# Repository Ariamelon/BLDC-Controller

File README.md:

# BLDC motor controller
A brushless DC motor controller developed in partial fulfilment of the requirements for a degree of BEng (Hons) Electronic & Computer Engineering.

## Disclaimer
The hardware is licensed under CERN-OHL-S-2.0, and the firmware is licensed under GNU GPLv3. 

https://github.com/user-attachments/assets/5595b5e6-1121-481e-8a8e-658866d14e04

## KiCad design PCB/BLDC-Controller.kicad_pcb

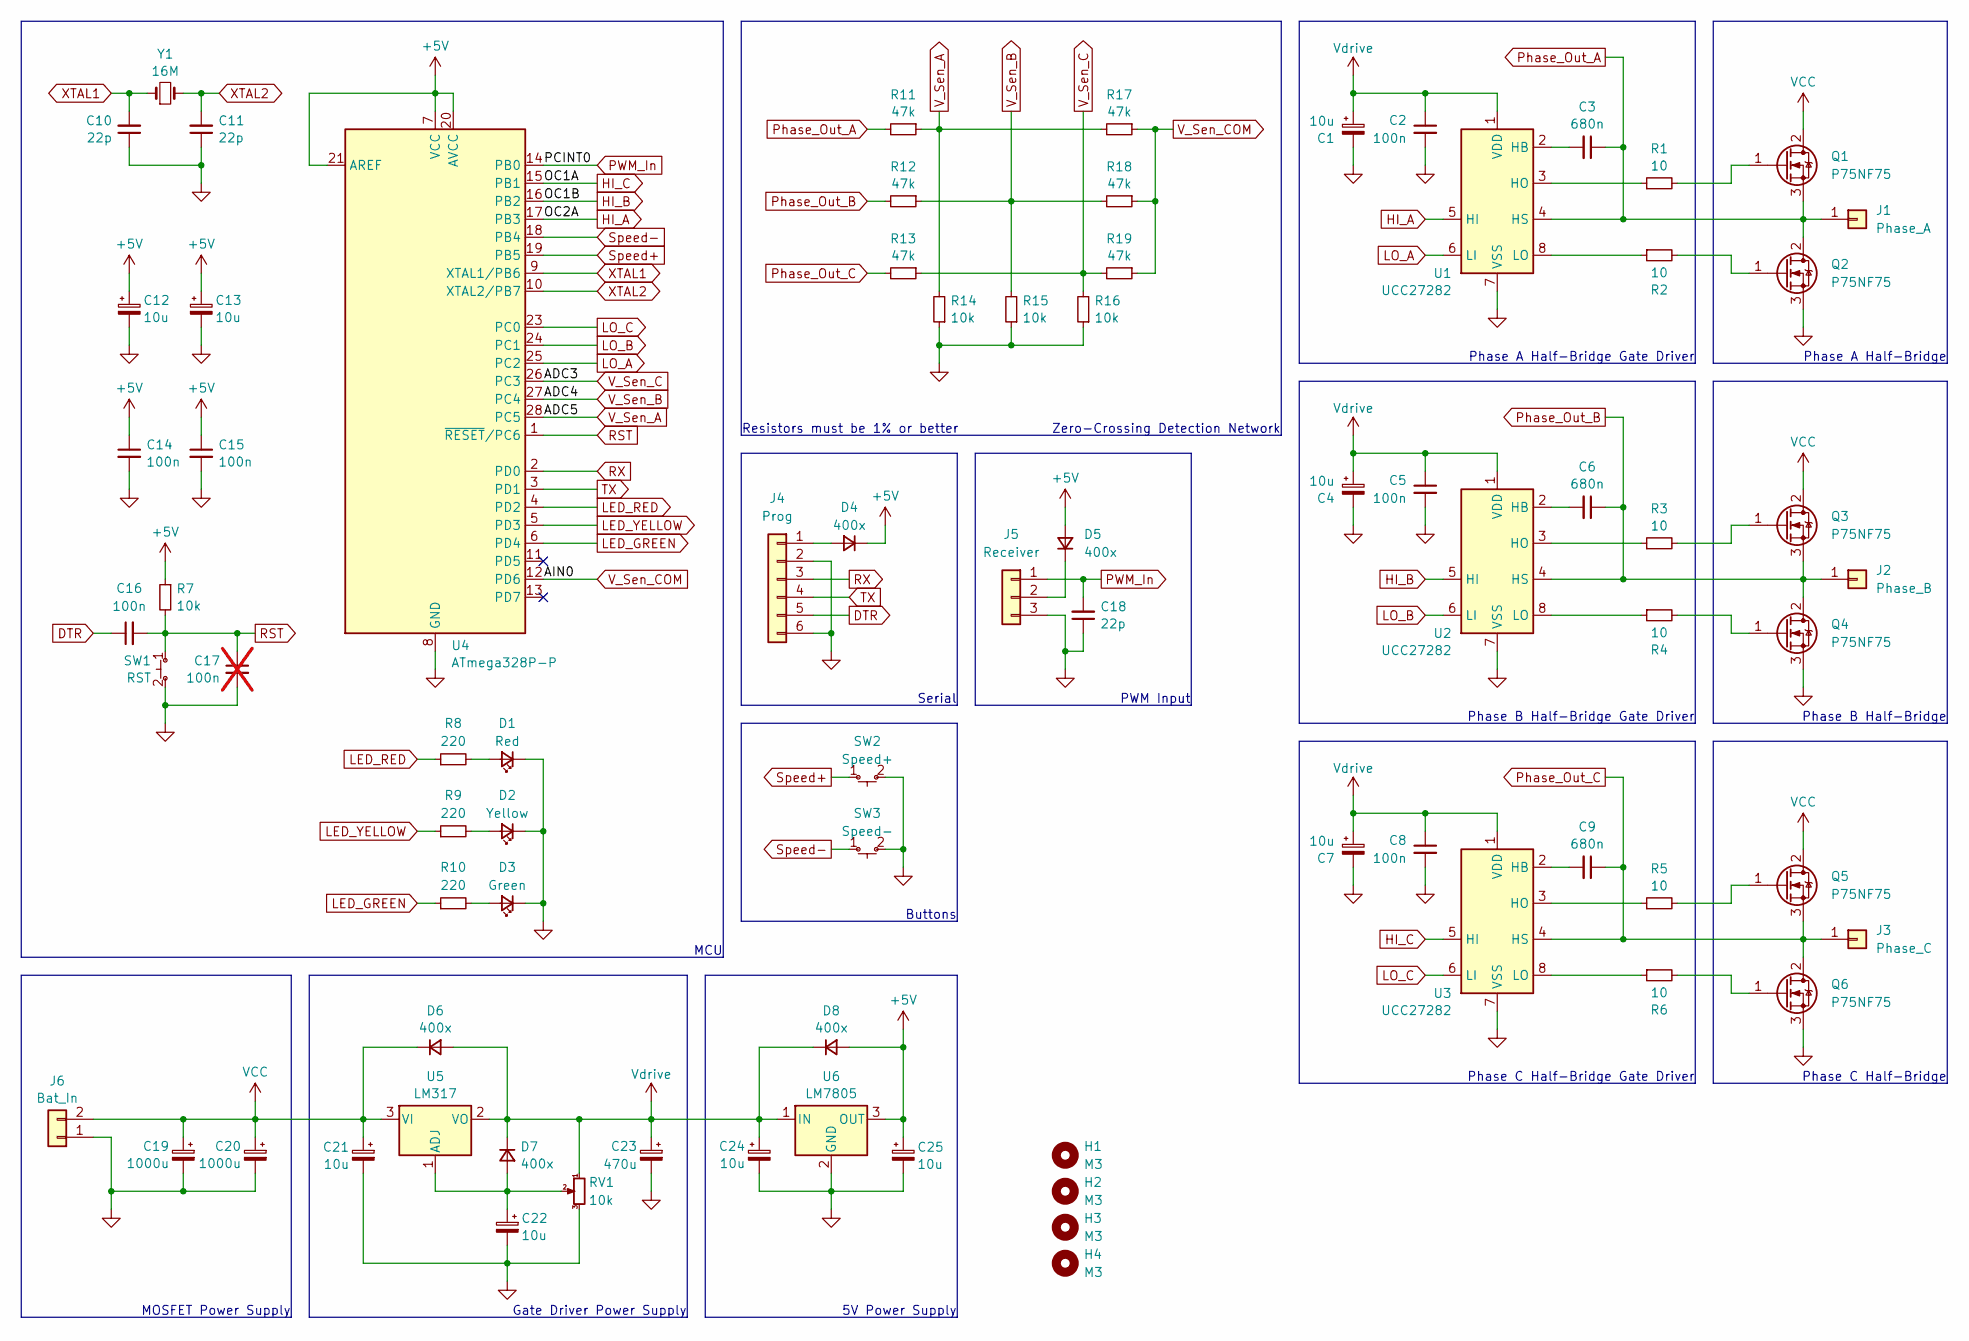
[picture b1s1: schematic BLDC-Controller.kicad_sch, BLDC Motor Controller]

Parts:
C1, C4, C7, C12, C13, C21, C22, C24, C25: 10u; CP_Radial_D5.0mm_P2.54mm
C2, C5, C8, C14, C15, C16: 100n; C_Disc_D6.0mm_W2.5mm_P5.08mm
C3, C6, C9: 680n; C_Rect_L7.0mm_W4.5mm_P5.08mm
C10, C11, C18: 22p; C_Disc_D5.0mm_W2.5mm_P2.54mm
C17: 100n; C_Disc_D6.0mm_W2.5mm_P5.08mm; not fitted
C19, C20: 1000u; CP_Radial_D16.0mm_P7.62mm
C23: 470u; CP_Radial_D10.0mm_P5.00mm
D1: Red; LED_D3.0mm
D2: Yellow; LED_D3.0mm
D3: Green; LED_D3.0mm
D4, D5, D6, D7, D8: 400x; D_DO-35_SOD27_P7.62mm_Horizontal
H1, H2, H3, H4: M3; MountingHole_3.2mm_M3_Pad
J1: Phase_A; TestPoint_Pad_4.0x4.0mm
J2: Phase_B; TestPoint_Pad_4.0x4.0mm
J3: Phase_C; TestPoint_Pad_4.0x4.0mm
J4: Prog; PinHeader_1x06_P2.54mm_Vertical
J5: Receiver; PinHeader_1x03_P2.54mm_Vertical
J6: Bat_In; AMASS_XT60-M_1x02_P7.20mm_Vertical
Q1, Q2, Q3, Q4, Q5, Q6: P75NF75; TO-220-3_Vertical
R1, R2, R3, R4, R5, R6: 10; R_Axial_DIN0204_L3.6mm_D1.6mm_P7.62mm_Horizontal
R7, R14, R15, R16: 10k; R_Axial_DIN0204_L3.6mm_D1.6mm_P7.62mm_Horizontal
R8, R9, R10: 220; R_Axial_DIN0204_L3.6mm_D1.6mm_P7.62mm_Horizontal
R11, R12, R13, R17, R18, R19: 47k; R_Axial_DIN0204_L3.6mm_D1.6mm_P7.62mm_Horizontal
RV1: 10k; Potentiometer_Piher_PT-10-V10_Vertical
SW1: RST; SW_PUSH_6mm
SW2: Speed+; SW_PUSH_6mm
SW3: Speed-; SW_PUSH_6mm
U1, U2, U3: UCC27282; DIP-8_W7.62mm_Socket
U4: ATmega328P-P; DIP-28_W7.62mm_Socket
U5: LM317; TO-220-3_Vertical
U6: LM7805; TO-220-3_Vertical
Y1: 16M; Crystal_HC49-4H_Vertical

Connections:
+5V: C12.1, C13.1, C14.1, C15.1, C25.1, D4.1 (K), D5.2 (A), D8.2 (A), R7.1, U4.7 (VCC), U4.20 (AVCC), U4.21 (AREF), U6.3 (OUT)
DTR: C16.1, J4.5
GND: C1.2, C2.2, C4.2, C5.2, C7.2, C8.2, C10.1, C11.1, C12.2, C13.2, C14.2, C15.2, C17.2, C18.1, C19.2, C20.2, C21.2, C22.2, C23.2, C24.2, C25.2, D1.1 (K), D2.1 (K), D3.1 (K), J4.2, J4.6, J5.3, J6.1, Q2.3 (S), Q4.3 (S), Q6.3 (S), R14.1, R15.1, R16.1, RV1.3, SW1.2 (B), SW2.2 (B), SW3.2 (B), U1.7 (VSS), U1.9 (EP), U2.7 (VSS), U2.9 (EP), U3.7 (VSS), U3.9 (EP), U4.8 (GND), U4.22 (GND), U6.2 (GND)
HI_A: U1.5 (HI), U4.17 (PB3)
HI_B: U2.5 (HI), U4.16 (PB2)
HI_C: U3.5 (HI), U4.15 (PB1)
LED_GREEN: R10.1, U4.6 (PD4)
LED_RED: R8.1, U4.4 (PD2)
LED_YELLOW: R9.1, U4.5 (PD3)
LO_A: U1.6 (LI), U4.25 (PC2)
LO_B: U2.6 (LI), U4.24 (PC1)
LO_C: U3.6 (LI), U4.23 (PC0)
unnamed: D1.2 (A), R8.2
unnamed: D2.2 (A), R9.2
unnamed: D3.2 (A), R10.2
unnamed: D4.2 (A), J4.1
unnamed: D5.1 (K), J5.2
unnamed: C22.1, D7.2 (A), RV1.2, U5.1 (ADJ)
unnamed: Q1.1 (G), R1.2
unnamed: Q2.1 (G), R2.2
unnamed: Q3.1 (G), R3.2
unnamed: Q4.1 (G), R4.2
unnamed: Q5.1 (G), R5.2
unnamed: Q6.1 (G), R6.2
unnamed: C3.2, U1.2 (HB)
unnamed: R1.1, U1.3 (HO)
unnamed: R2.1, U1.8 (LO)
unnamed: C6.2, U2.2 (HB)
unnamed: R3.1, U2.3 (HO)
unnamed: R4.1, U2.8 (LO)
unnamed: C9.2, U3.2 (HB)
unnamed: R5.1, U3.3 (HO)
unnamed: R6.1, U3.8 (LO)
PWM_In: C18.2, J5.1, U4.14 (PB0)
Phase_Out_A: C3.1, J1.1, Q1.3 (S), Q2.2 (D), R11.2, U1.4 (HS)
Phase_Out_B: C6.1, J2.1, Q3.3 (S), Q4.2 (D), R12.2, U2.4 (HS)
Phase_Out_C: C9.1, J3.1, Q5.3 (S), Q6.2 (D), R13.2, U3.4 (HS)
RST: C16.2, C17.1, R7.2, SW1.1 (A), U4.1 (~RESET/PC6)
RX: J4.3, U4.2 (PD0)
Speed+: SW2.1 (A), U4.19 (PB5)
Speed-: SW3.1 (A), U4.18 (PB4)
TX: J4.4, U4.3 (PD1)
VCC: C19.1, C20.1, C21.1, D6.1 (K), J6.2, Q1.2 (D), Q3.2 (D), Q5.2 (D), U5.3 (VI)
V_Sen_A: R11.1, R14.2, R17.2, U4.28 (PC5)
V_Sen_B: R12.1, R15.2, R18.2, U4.27 (PC4)
V_Sen_C: R13.1, R16.2, R19.2, U4.26 (PC3)
V_Sen_COM: R17.1, R18.1, R19.1, U4.12 (PD6)
Vdrive: C1.1, C2.1, C4.1, C5.1, C7.1, C8.1, C23.1, C24.1, D6.2 (A), D7.1 (K), D8.1 (K), RV1.1, U1.1 (VDD), U2.1 (VDD), U3.1 (VDD), U5.2 (VO), U6.1 (IN)
XTAL1: C10.2, U4.9 (XTAL1/PB6), Y1.1
XTAL2: C11.2, U4.10 (XTAL2/PB7), Y1.2

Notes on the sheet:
MOSFET Power Supply
Gate Driver Power Supply
Resistors must be 1% or better
5V Power Supply
PWM Input
Buttons
Phase A Half-Bridge Gate Driver
Serial
Zero-Crossing Detection Network
Phase C Half-Bridge Gate Driver
Phase C Half-Bridge
Phase A Half-Bridge
Phase B Half-Bridge
Phase B Half-Bridge Gate Driver
MCU

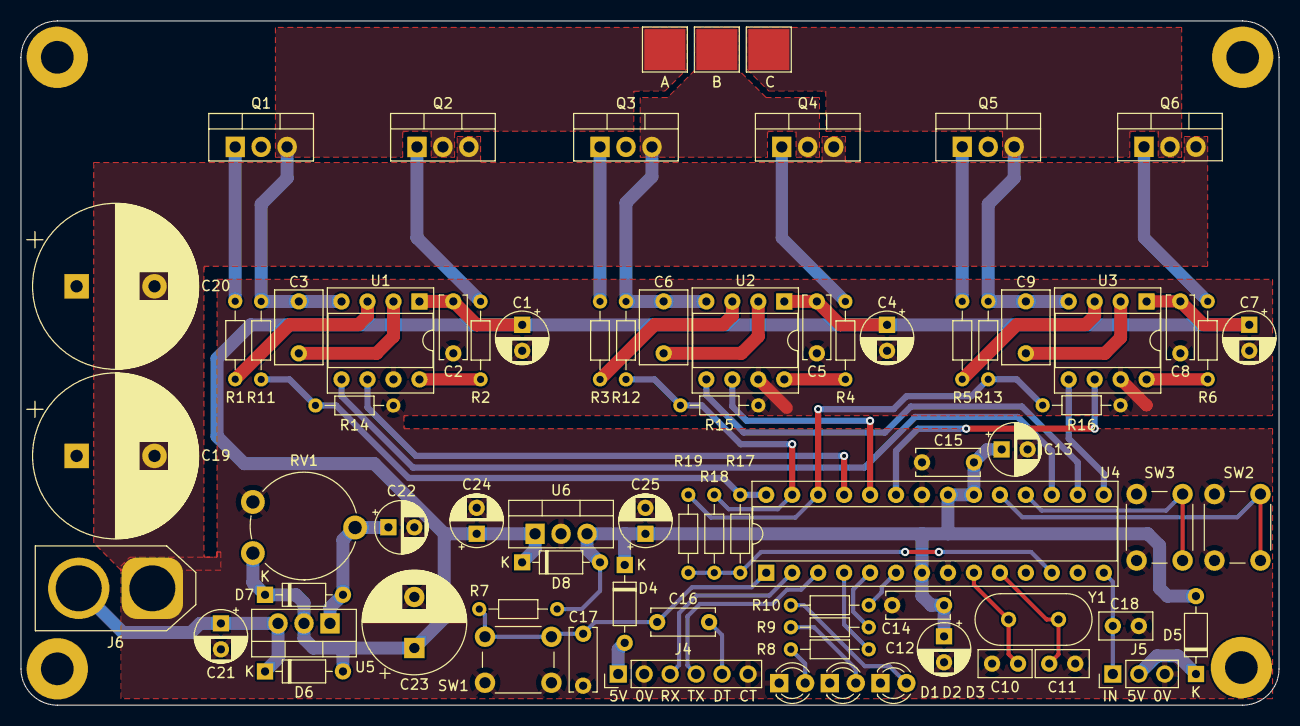
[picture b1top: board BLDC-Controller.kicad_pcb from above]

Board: 2 copper layers, 123.1 x 66.9 mm, 80 parts (0 on the bottom side), 50 nets.

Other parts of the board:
A1: Art; Ariamelon_Logo_Large_Mask

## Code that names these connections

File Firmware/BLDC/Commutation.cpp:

/*
This file is part of BLDC control firmware.

BLDC control firmware is free software: you can redistribute it and/or modify it
under the terms of the GNUGeneral Public License as published by the Free Software
Foundation, either version 3 of the License, or (at your option) any later version.

BLDC control firmware is distributed in the hope that it will be useful,
but WITHOUT ANY WARRANTY; without even the implied warranty of MERCHANTABILITY or
FITNESS FOR A PARTICULAR PURPOSE. See the GNU General Public License for more details.

You should have received a copy of the GNU General Public License along with BLDC control firmware.
If not, see <https://www.gnu.org/licenses/>. 
*/

#include "Arduino.h"
#include "Commutation.h"

void initialize_controller(void){
  DDRB   |= 0b00001110; // Configure HI_A (PB3), HI_B (PB2) and HI_C (PB1) (high side) as outputs.
  PORTB  &= 0b11110001; // Disable HI_A (PB3), HI_B (PB2) and HI_C (PB1).
  PORTB  |= 0b00110000; // Enable speed+ (PB5) and speed- (PB4) pullups.

  DDRC   |= 0b00000111; // Configure LO_A (PC2), LO_B (PC1) and LO_C (PC0) (low side) as outputs.
  PORTC  &= 0b11111000; // Disable LO_A (PC2), LO_B (PC1) and LO_C (PC0).
  
  DDRD   |= 0b00011100; // Configure red LED (PD2), yellow LED (PD3) and green LED (PD4) as outputs.
  PORTD  &= 0b11100111; // Disable yellow LED (PD3) and green LED (PD4).
  PORTD  |= 0b00000100; // Enable red LED (PD2).

  TCCR1A  = 0;          // Initialize timers 1 and 2.
  TCCR1B  = 0b00000001; // Clock source set to clkIO / 1 (no prescaling).
  TCCR2A  = 0;          // Allows for highest PWM frequency.
  TCCR2B  = 0b00000001; // Also disable PWM outputs.

  ACSR    = 0b00010000; // Disable and clear ACI flag (analog comparator interrupt).
  ADCSRA  = 0;          // Disable ADC.
}

unsigned char motor_start(unsigned char pwm_lowest_duty, unsigned char old_step, unsigned char input_voltage){
  Serial.print("Starting up motor. ");
  PORTD |= 0b00001000;  // Enable yellow LED (PD3).

  // Acceleration rate depends on duty cycle and input voltage.
  unsigned int delay_duration = OPEN_LOOP_DELAY;
  unsigned int delay_factor = 70;
  unsigned char pwm_start_duty = delay_factor - input_voltage;

  pwm_duty_set(pwm_start_duty);
  unsigned char new_step = old_step;

  new_step = commutation_step_set(new_step);  // Starts up motor even when rotor is still moving.
  delay(ALIGN_MS);

  // Open-loop commutation.
  pwm_duty_set(pwm_start_duty);
  while (delay_duration > 3000 / (input_voltage + 5)){
    new_step = commutation_step_set(new_step);
    delayMicroseconds(delay_duration);
    delay_duration -= delay_factor;
  }

  PORTD &= 0b11110111;  // Disable yellow LED (PD3).
  PORTD |= 0b00010000;  // Enable green LED (PD4).

  ACSR   = 0b00011000;  // Enable analog comparator interrupt and clear ACI flag.
  ADCSRB = 0b01000000;  // Enable analog comparator mux.
  return new_step;
}

void motor_stop(void){
  Serial.print("Shutting down motor. ");
  PORTD &= 0b11101111;  // Disable green LED (PD4).

  PORTC &= 0b11111000;  // Disable LO_A (PC2), LO_B (PC1) and LO_C (PC0).

  TCCR1A = 0;           // Disable HI_C (0C1A) and HI_B (OC1B).
  TCCR2A = 0;           // Disable HI_A (OC2A).

  ADCSRB = 0;           // Disable analog comparator mux.
  ACSR   = 0b00010000;  // Disable analog comparator interrupt and clear analog comparator interrupt flag.
}

unsigned char commutation_step_set(unsigned char current_step){ // BLDC motor commutation function.
  switch(current_step){
    case 0:
      PORTC &= 0b11111010;  // Disable LO_A (PC2) and LO_C (PC0).
      PORTC |= 0b00000010;  // Enable LO_B (PC1).

      TCCR1A = 0;           // Disable HI_C (0C1A) and HI_B (OC1B).
      TCCR2A = 0b10000001;  // Enable HI_A (OC2A) in PWM, phase correct, 8-bit mode.

      ADMUX  = 0b00000011;  // Select V_Sen_C (ADC3) as comparator inverting input.
      ACSR  |= 0b00000011;  // Set interrupt on rising edge.
      break;
    case 1:
      PORTC &= 0b11111001;  // Disable LO_A (PC2) and LO_B (PC1).
      PORTC |= 0b00000001;  // Enable LO_C (PC0).

      TCCR1A = 0;           // Disable HI_C (0C1A) and HI_B (OC1B).
      TCCR2A = 0b10000001;  // Enable HI_A (OC2A) in PWM, phase correct, 8-bit mode.

      ADMUX  = 0b00000100;  // Select V_Sen_B (ADC4) as comparator inverting input.
      ACSR  &= 0b11111110;  // Set interrupt on falling edge.
      break;
    case 2:
      PORTC &= 0b11111001;  // Disable LO_A (PC2) and LO_B (PC1).
      PORTC |= 0b00000001;  // Enable LO_C (PC0).

      TCCR2A = 0;           // Disable HI_A (OC2A).
      TCCR1A = 0b00100001;  // Enable HI_B (OC1B) in PWM, phase correct, 8-bit mode and disable HI_C (0C1A).
      
      ADMUX  = 0b00000101;  // Select V_Sen_A (PC5) as comparator inverting input.
      ACSR  |= 0b00000011;  // Set interrupt on rising edge.
      break;
    case 3:
      PORTC &= 0b11111100;  // Disable LO_B (PC1) and LO_C (PC0).
      PORTC |= 0b00000100;  // Enable LO_A (PC2).

      TCCR2A = 0;           // Disable HI_A (OC2A).
      TCCR1A = 0b00100001;  // Enable HI_B (OC1B) in PWM, phase correct, 8-bit mode and disable HI_C (0C1A).
      
      ADMUX  = 0b00000011;  // Select V_Sen_C (ADC3) as comparator inverting input.
      ACSR  &= 0b11111110;  // Set interrupt on falling edge.
      break;
    case 4:
      PORTC &= 0b11111100;  // Disable LO_B (PC1) and LO_C (PC0).
      PORTC |= 0b00000100;  // Enable LO_A (PC2).

      TCCR2A = 0;           // Disable HI_A (OC2A).
      TCCR1A = 0b10000001;  // Enable HI_C (0C1A) in PWM, phase correct, 8-bit mode and disable HI_B (OC1B).
      
      ADMUX  = 0b00000100;  // Select V_Sen_B (ADC4) as comparator inverting input.
      ACSR  |= 0b00000011;  // Set interrupt on rising edge.
      break;
    case 5:
      PORTC &= 0b11111010;  // Disable LO_A (PC2) and LO_C (PC0).
      PORTC |= 0b00000010;  // Enable LO_B (PC1).

      TCCR2A = 0;           // Disable HI_A (OC2A).
      TCCR1A = 0b10000001;  // Enable HI_C (0C1A) in PWM, phase correct, 8-bit mode and disable HI_B (OC1B).
            
      ADMUX  = 0b00000101;  // Select V_Sen_A (PC5) as comparator inverting input.
      ACSR  &= 0b11111110;  // Set interrupt on falling edge.
      break;
  }
  unsigned char next_step = current_step + 1;
  next_step %= 6;
  return next_step;
}

void pwm_duty_set(unsigned char duty){
  OCR1A = OCR1B = OCR2A = duty; // Set PWM duty cycle for all outputs.
}

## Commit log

2023-10-23 First draft of schematic done.
2023-10-28 28/10/2023 update
    Began initial PCB layout.
2023-10-30 30/10/2023 update
    Completed initial PCB layout.
2024-02-13 Completed initial prototype.
2024-02-19 Fixed pin assignment. Added tentative arduino code.
2024-03-09 Uploaded working software.
2024-03-11 Revisions to code.
2024-03-12 V2 started
2024-03-13 Updated to V1.1. Removed extra parts. Rearranged components.
2024-03-13 Updated to V1.1. Removed extra parts. Rearranged components. Added on-board LEDs.
2024-03-14 Updated PCB for better grounding.
2024-03-22 Tentative code update to V1.1.
2024-03-24 Updated firmware.
2024-04-09 Fixed issues with code. Updated schematic.
2024-04-10 Uploaded images on system operation. Updated schematic.
2024-04-10 Updated schematic.
2024-05-03 Added diagrams. Updated code.
2024-05-05 Updated code.
2024-05-05 Updated schematic. Added new documentation.
2024-05-06 Added serial control to code. Separated functions to different files.
2024-05-18 Added new images. Modified schematic and PCB.
2024-05-20 Final update before project completion.
2024-10-13 Updated README.md. Added images and video.
2024-10-22 License updated to CERN-OHL-S-2.0.
2024-10-29 Added license for software. Specified which license applies to which.
2024-11-05 Removed extraneous details.
